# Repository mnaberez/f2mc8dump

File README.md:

# f2mc8dump

## Overview

Some Fujitsu F2MC-8L microcontrollers have an
external bus capability (see the [catalog](https://web.archive.org/web/20170514004456/http://www.fujitsu.com/downloads/MICRO/fme/micros/micros_2006.pdf)).
I found that the external bus can be used to dump the contents of the
internal ROM, which is not normally accessible.

A mode pin enables the external bus.  In this mode, the internal ROM is disabled and its address space is redirected
to the external bus.  I dumped the internal ROM of the several F2MC-8L microcontrollers by hooking up an external EPROM that wrote a dumping program into RAM, then jumped to RAM.  While code was executing from RAM, I changed the mode pin.  The external bus was disabled, the internal ROM was enabled, but code kept executing from RAM and dumped out the contents of the internal ROM.

## Tested

I developed this method to extract the firmware from the [Volkswagen Premium IV](https://github.com/mnaberez/vwradio) car radios made by Clarion.  These radios contain the following microcontrollers:

 - MB89623R
 - MB89625R
 - MB89677AR

I successfully extracted the internal ROM code from all of them.  I've also tried samples of the above chips from other products and was able to extract the code from them as well.

## Hardware

The hardware setup requires the F2MC-8L microcontroller be removed from the
target device. It is placed on a board with the following other components:

 - 2764 or similar parallel EPROM with dumping firmware
 - 74HCT373 transparent latch
 - 74HCT138 3-8 decoder
 - 5V TTL oscillator (1-8 MHz)
 - 5V regulator, decoupling caps, pull-up resistors, etc.

See the `hardware/` directory for details.

A logic analyzer with 9 probes (8 data lines, 1 strobe line) is required to
capture the output from the dumping hardware.

## Firmware

Assemble the dumping firmware in the `firmware/` directory using the [asf2mc8](http://shop-pdp.net/ashtml/asf2mc.htm)
assembler and burn it into the EPROM.

## Dump

Build the hardware and power it up in external bus mode (MOD0=Vcc). It will
immediately begin dumping the memory space out P30-P37 with /STROBE on P40
after each byte. It will wrap around memory and keep dumping forever. If you
capture it with a logic analyzer, you'll see the string `EXTERNALROM` from
the dumping firmware.

While power is still applied, change MOD0 to Vss. This selects the internal
ROM mode. The program will continue dumping but it will now be dumping the
internal ROM instead. Capture the output with a logic analyzer and let it
run for a couple minutes so the entire memory space is dumped several times.
Save the capture to a file.

Use the Python script under the `host/` directory to split individual
ROM images from the logic analyzer capture.

## Disassemble

After a binary has been obtained, use [f2mc8dasm](https://github.com/mnaberez/f2mc8dasm) to disassemble it.

## Author

[Mike Naberezny](https://github.com/mnaberez)

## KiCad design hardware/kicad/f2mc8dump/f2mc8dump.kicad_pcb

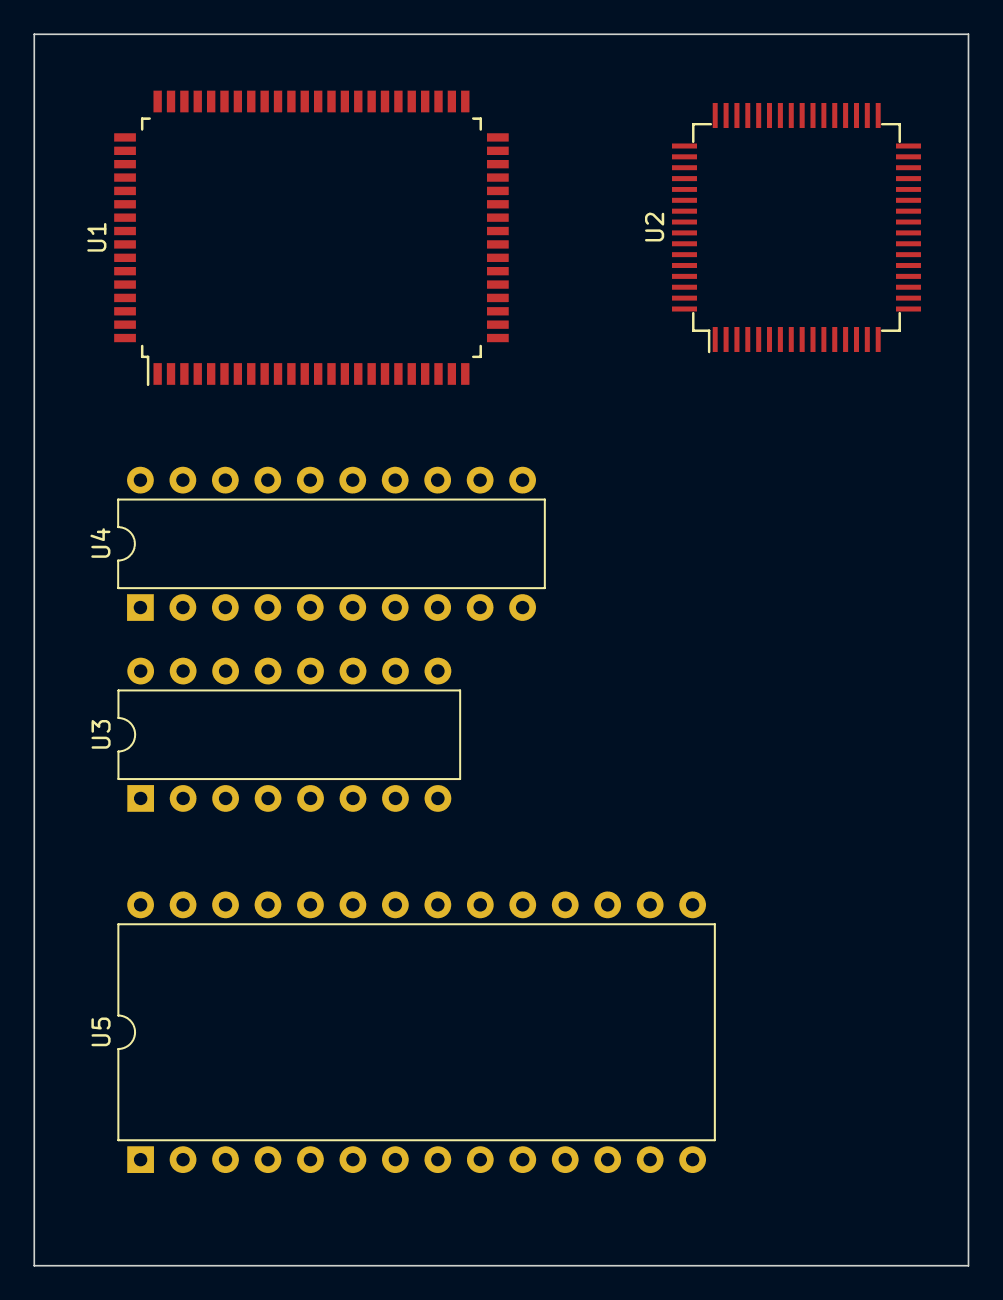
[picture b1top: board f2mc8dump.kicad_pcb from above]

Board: 2 copper layers, 55.9 x 73.7 mm, 5 parts (0 on the bottom side), 30 nets, no tracks yet.

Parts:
U1: MB89677AR; PQFP-80_14x20mm_P0.8mm
U2: MB89623R; PQFP-64_12x12mm_P0.65mm
U3: 74LS138; DIP-16_W7.62mm
U4: 74LS373; DIP-20_W7.62mm
U5: 2764; DIP-28_W15.24mm

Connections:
A08: U1.32 (P10/A08), U2.40 (P10/A08)
A09: U1.31 (P11/A09), U2.39 (P11/A09)
A10: U1.30 (P12/A10), U2.38 (P12/A10), U5.21 (A10)
A11: U1.29 (P13/A11), U2.37 (P13/A11), U5.23 (A11)
A12: U1.28 (P14/A12), U2.36 (P14/A12), U5.2 (A12)
A13: U1.27 (P15/A13), U2.35 (P15/A13), U3.1 (A0)
A14: U1.26 (P16/A14), U2.34 (P16/A14), U3.2 (A1)
A15: U1.25 (P17/A15), U2.33 (P17/A15), U3.3 (A2)
AD0: U1.40 (P00/AD0), U2.48 (P00/AD0), U4.3 (D0), U5.19 (D7)
AD1: U1.39 (P01/AD1), U2.47 (P01/AD1), U4.4 (D1), U5.18 (D6)
AD2: U1.38 (P02/AD2), U2.46 (P02/AD2), U4.7 (D2), U5.17 (D5)
AD3: U1.37 (P03/AD3), U2.45 (P03/AD3), U4.8 (D3), U5.16 (D4)
AD4: U1.36 (P04/AD4), U2.44 (P04/AD4), U4.13 (D4), U5.15 (D3)
AD5: U1.35 (P05/AD5), U2.43 (P05/AD5), U4.14 (D5), U5.13 (D2)
AD6: U1.34 (P06/AD6), U2.42 (P06/AD6), U4.17 (D6), U5.12 (D1)
AD7: U1.33 (P07/AD7), U2.41 (P07/AD7), U4.18 (D7), U5.11 (D0)
ALE: U1.17 (P27/ALE), U4.11 (LE)
GND: U1.12 (MOD1), U1.15 (VSS), U1.78 (AVR), U1.79 (AVSS), U2.12 (AVR), U2.13 (AVSS), U2.21 (MOD1), U2.24 (VSS), U3.4 (E1), U3.5 (E2), U3.8 (GND), U4.1 (OE), U4.10 (GND), U5.14 (GND)
MOD0: U1.11 (MOD0), U2.20 (MOD0), U3.6 (E3)
NRD: U1.18 (P26/NRD), U2.26 (P26/NRD), U5.22 (~OE)
unnamed: U3.7 (O7), U5.20 (~CE)
unnamed: U4.2 (O0), U5.10 (A0)
unnamed: U4.5 (O1), U5.9 (A1)
unnamed: U4.6 (O2), U5.8 (A2)
unnamed: U4.9 (O3), U5.7 (A3)
unnamed: U4.12 (O4), U5.6 (A4)
unnamed: U4.15 (O5), U5.5 (A5)
unnamed: U4.16 (O6), U5.4 (A6)
unnamed: U4.19 (O7), U5.3 (A7)
VCC: U1.77 (AVCC), U2.11 (AVCC), U2.56 (VCC), U3.16 (VCC), U4.20 (VCC), U5.1 (VPP), U5.27 (~PGM), U5.28 (VCC)

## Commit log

2018-01-13 Initial import
2018-01-13 Add photo of hardware
2018-01-13 Fix typo in README
2018-01-13 Rename file so it renders as Markdown
2018-01-13 Add license (BSD 3-clause)
2018-01-13 List specific chips tested
2018-01-16 Remove duplicate filename
2018-01-16 Ignore build files
2018-01-16 Add script to create binary from asf2mc8 listing
2018-02-12 Fix link to asf2mc8
2018-02-20 Explictly list chips tested in README
2018-02-20 Add a link to f2mc8dasm
2018-02-20 Fix typo in "F2MC-8L"
2018-02-28 Convert tabs to spaces
2018-02-28 Use symbols instead of hardcoded addresses
2018-03-28 Fix lst2bin on asf2mc8 v5.20
2018-03-28 Add config file for travis
2018-03-28 Add link to vwradio repo
2018-09-08 Build output binary using aslink and srec_cat
2019-01-30 Build using asxxxx fork on travis
2019-03-20 Build using asxxxx 5.31
2021-01-03 Add workflow for GitHub Actions
2022-01-11 Install asxxxx from GitHub
2022-01-12 Build using ASxxxx 5.40 Update 4 (2021-12-16)
2022-06-10 Upload build artifacts
2022-10-29 Upgrade GitHub Actions steps to fix deprecation warnings
2023-06-01 Ignore KiCad backups and preferences
2023-06-01 Start design in KiCad
2023-10-13 Build using ASxxxx 5.50
2026-05-29 Upgrade outdated GitHub Actions
